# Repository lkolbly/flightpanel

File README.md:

DIY Flightpanel
===============

Welcome to my DIY flightpanel. There are three components to this project:

* Mechanical design
* PCB design
* Firmware

All three are custom-built for this project.

PCB
===

The PCB has support for up to the following inputs:

* 16x push buttons
* 14x double-throw switches
* 6x rotary encoders with push-buttons
* 10x potentiometers or hall-effect sensors

(note that Windows only supports up to 8 axes)

Mechanical
==========

The mechanical design is in FreeCAD, in the `flightpanel.FCStd` file. Within
that project look at the Assembly for a reference design with all included
components, including stand-ins for various knobs and switches.

The design is oriented around providing a standardized base, with swappable
control scheme panels. Each panel has a working area of 60mm wide by 100mm tall
- see BigPanelTemplate in the FreeCAD project for a template. Two panels may be
combined to create a "wide" 128mm by 100mm panel.

The panel should extend 3.5mm past the centers of the holes for optimum
mechanical support.

The core structure provides space for up to 6 panels - two on the front face,
two on the top face (with an approximately 30 degree slope), and one on each
side.

The core consists of the following parts:
- `StructureFront`
- `StructureTop`
- `StructureBase`
- `SidePanel`

The mounting on the back is two M6 holes spaced 40mm apart vertically. Mouse bites are provided for additional rigidity. The `Mount` part provides a reference design for a mount - as modelled, for mounting to a 35mm wide square tube.

Hardware required for assembly:
- Heat-set M3 threaded inserts, designed for a 4.5mm diameter hole with 5mm depth.
- 14 to 38x M3 by 8mm bolts (14 for structure assembly, up to 24 for mounting panels).
- 2x M6 by 20mm bolts with nuts.

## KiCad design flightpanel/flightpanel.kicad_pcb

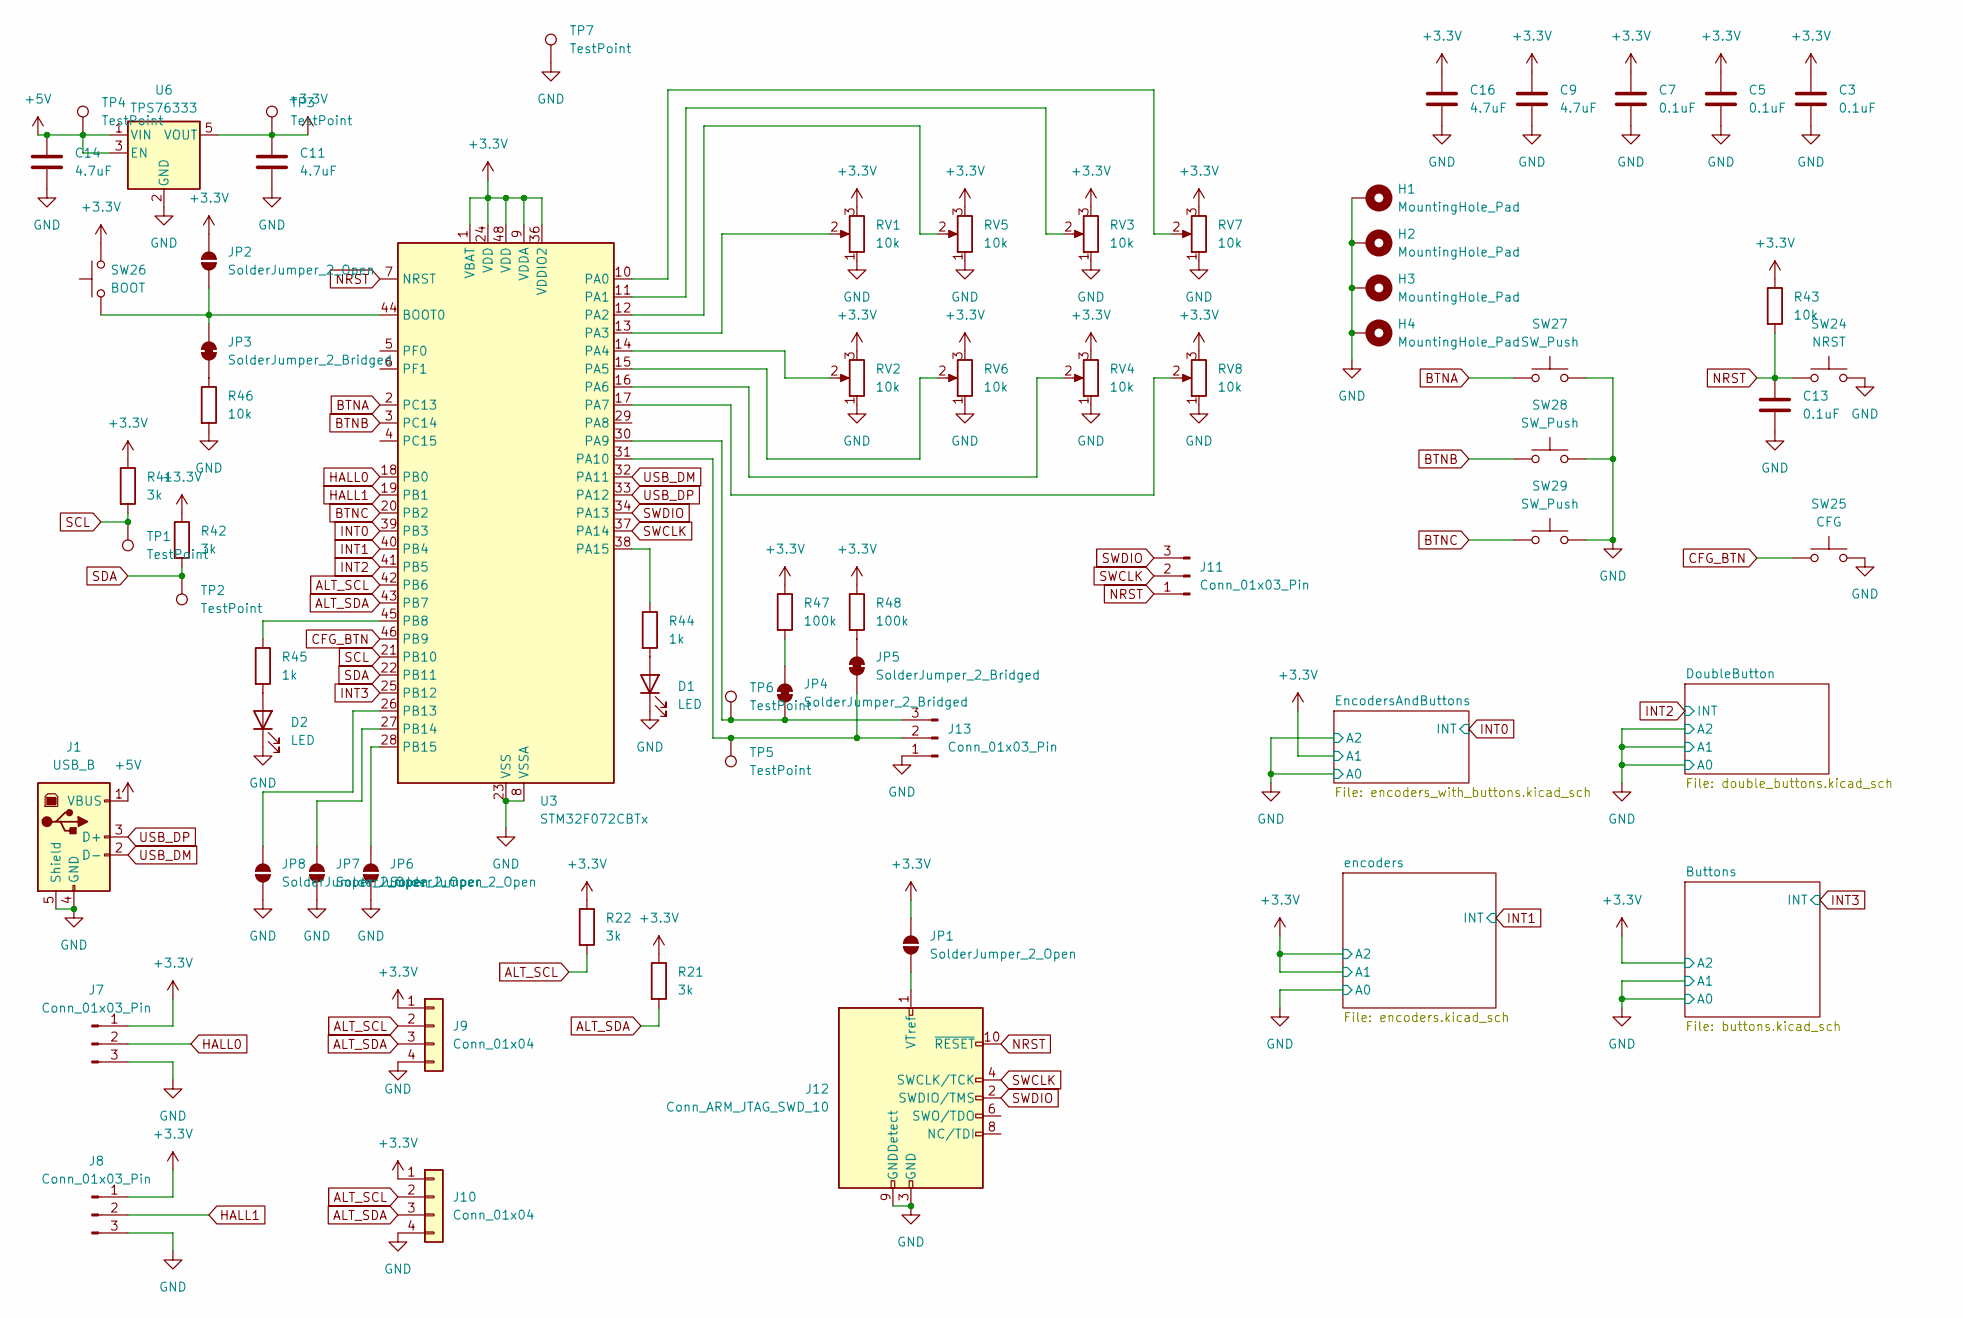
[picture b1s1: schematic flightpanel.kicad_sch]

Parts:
C3, C5, C7, C13: 0.1uF; C_0603_1608Metric; LCSC Part Number C14663
C9, C11, C14, C16: 4.7uF; C_0603_1608Metric; LCSC Part Number C19666
D1, D2: LED; LED_0603_1608Metric; LCSC Part Number C2286
H1, H2, H3, H4: MountingHole_Pad; MountingHole_3.2mm_M3_Pad
J1: USB_B; USB-B-TH_USB-B10-BRW; LCSC Part Number C720549
J7, J8, J11: Conn_01x03_Pin; PinHeader_1x03_P2.54mm_Vertical
J9, J10: Conn_01x04; PinHeader_1x04_P2.54mm_Vertical
J12: Conn_ARM_JTAG_SWD_10; PinHeader_2x05_P1.27mm_Vertical; LCSC Part Number C239059
J13: Conn_01x03_Pin; PinHeader_1x03_P2.54mm_Vertical; LCSC Part Number C146690
JP1, JP2, JP6, JP7, JP8: SolderJumper_2_Open; SolderJumper-2_P1.3mm_Open_RoundedPad1.0x1.5mm
JP3, JP4, JP5: SolderJumper_2_Bridged; SolderJumper-2_P1.3mm_Bridged_RoundedPad1.0x1.5mm
R21, R22, R41, R42: 3k; R_0603_1608Metric; LCSC Part Number C4211
R43, R46: 10k; R_0603_1608Metric; LCSC Part Number C25804
R44, R45: 1k; R_0603_1608Metric; LCSC Part Number C21190
R47, R48: 100k; R_0603_1608Metric; LCSC Part Number C25803
RV1, RV2, RV3, RV4, RV5, RV6, RV7, RV8: 10k; PinSocket_1x03_P2.54mm_Vertical; LCSC Part Number C146690
SW24: NRST; SW-SMD_L3.9-W3.0-P4.45; LCSC Part Number C720477
SW25: CFG; SW-SMD_L3.9-W3.0-P4.45; LCSC Part Number C720477
SW26: BOOT; SW-SMD_L3.9-W3.0-P4.45; LCSC Part Number C720477
SW27, SW28, SW29: SW_Push; PinSocket_1x02_P2.54mm_Vertical; LCSC Part Number C49661
TP1, TP2, TP3, TP4, TP5, TP6, TP7: TestPoint; TestPoint_Pad_D2.0mm
U3: STM32F072CBTx; LQFP-48_7x7mm_P0.5mm; LCSC Part Number C81720
U6: TPS76333; SOT-23-5; LCSC Part Number C7100

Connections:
+3.3V: C3.1, C5.1, C7.1, C9.1, C11.1, C16.1, J7.1, J8.1, J9.1, J10.1, JP1.2 (B), JP2.2 (B), R21.1, R22.1, R41.1, R42.1, R43.1, R47.1, R48.1, RV1.3, RV2.3, RV3.3, RV4.3, RV5.3, RV6.3, RV7.3, RV8.3, SW26.2, TP3.1, U3.1 (VBAT), U3.9 (VDDA), U3.24 (VDD), U3.36 (VDDIO2), U3.48 (VDD), U6.5 (VOUT); also elsewhere on the board
+5V: C14.1, J1.1 (VBUS), TP4.1, U6.1 (VIN), U6.3 (EN)
ALT_SCL: J9.2, J10.2, R22.2, U3.42 (PB6)
ALT_SDA: J9.3, J10.3, R21.2, U3.43 (PB7)
BTNA: SW27.1, U3.2 (PC13)
BTNB: SW28.1, U3.3 (PC14)
BTNC: SW29.1, U3.20 (PB2)
CFG_BTN: SW25.1, U3.46 (PB9)
GND: C3.2, C5.2, C7.2, C9.2, C11.2, C13.2, C14.2, C16.2, D1.1 (K), D2.1 (K), H1.1, H2.1, H3.1, H4.1, J1.4 (GND), J1.5 (Shield), J7.3, J8.3, J9.4, J10.4, J12.3 (GND), J12.5 (GND), J12.9 (GNDDetect), J13.1, JP6.1 (A), JP7.1 (A), JP8.1 (A), R46.2, RV1.1, RV2.1, RV3.1, RV4.1, RV5.1, RV6.1, RV7.1, RV8.1, SW24.2, SW25.2, SW27.2, SW28.2, SW29.2, TP7.1, U3.8 (VSSA), U3.23 (VSS), U3.35 (VSS), U3.47 (VSS), U6.2 (GND); also elsewhere on the board
HALL0: J7.2, U3.18 (PB0)
HALL1: J8.2, U3.19 (PB1)
INT0: U3.39 (PB3); also elsewhere on the board
INT1: U3.40 (PB4); also elsewhere on the board
INT2: U3.41 (PB5); also elsewhere on the board
INT3: U3.25 (PB12); also elsewhere on the board
NRST: C13.1, J11.1, J12.10 (~RESET), R43.2, SW24.1, U3.7 (NRST)
unnamed: D1.2 (A), R44.2
unnamed: D2.2 (A), R45.2
unnamed: J12.1 (VTref), JP1.1 (A)
unnamed: J13.2, JP5.1 (A), TP5.1, U3.31 (PA10)
unnamed: J13.3, JP4.1 (A), TP6.1, U3.30 (PA9)
unnamed: JP2.1 (A), JP3.2 (B), SW26.1, U3.44 (BOOT0)
unnamed: JP3.1 (A), R46.1
unnamed: JP4.2 (B), R47.2
unnamed: JP5.2 (B), R48.2
unnamed: JP6.2 (B), U3.28 (PB15)
unnamed: JP7.2 (B), U3.27 (PB14)
unnamed: JP8.2 (B), U3.26 (PB13)
unnamed: RV7.2, U3.10 (PA0)
unnamed: RV3.2, U3.11 (PA1)
unnamed: RV5.2, U3.12 (PA2)
unnamed: RV1.2, U3.13 (PA3)
unnamed: RV2.2, U3.14 (PA4)
unnamed: RV6.2, U3.15 (PA5)
unnamed: RV4.2, U3.16 (PA6)
unnamed: RV8.2, U3.17 (PA7)
unnamed: R44.1, U3.38 (PA15)
unnamed: R45.1, U3.45 (PB8)
SCL: R41.2, TP1.1, U3.21 (PB10); also elsewhere on the board
SDA: R42.2, TP2.1, U3.22 (PB11); also elsewhere on the board
SWCLK: J11.2, J12.4 (SWCLK/TCK), U3.37 (PA14)
SWDIO: J11.3, J12.2 (SWDIO/TMS), U3.34 (PA13)
USB_DM: J1.2 (D-), U3.32 (PA11)
USB_DP: J1.3 (D+), U3.33 (PA12)

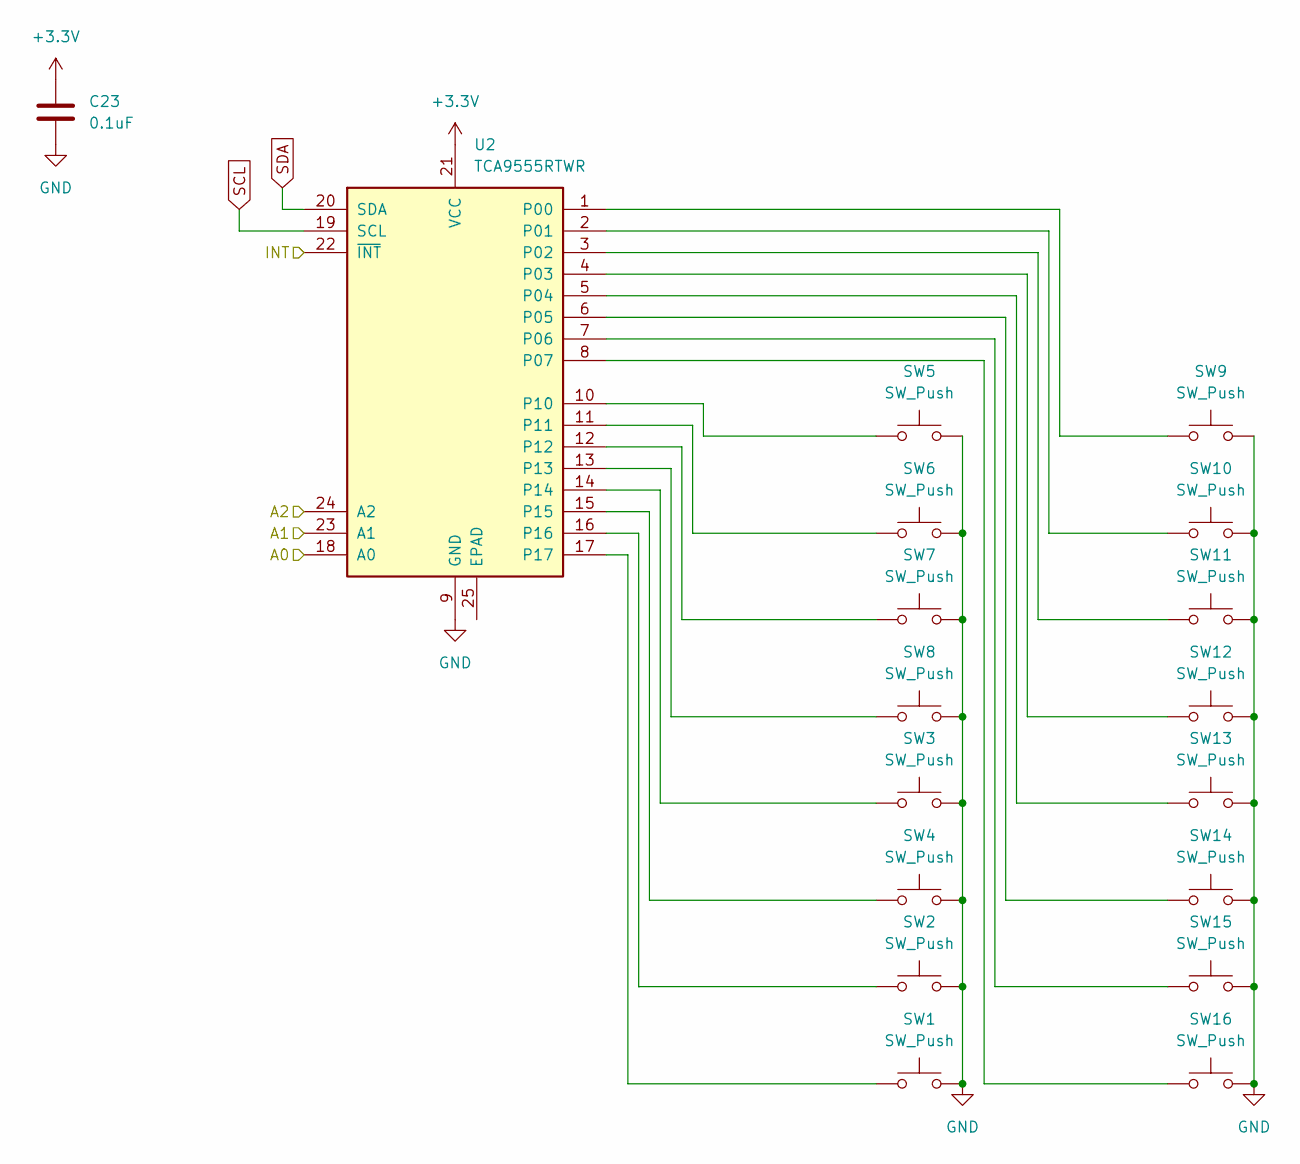
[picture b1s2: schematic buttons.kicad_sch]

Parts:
C23: 0.1uF; C_0603_1608Metric; LCSC Part Number C14663
SW1, SW2, SW3, SW4, SW5, SW6, SW7, SW8, SW9, SW10, SW11, SW12, SW13, SW14, SW15, SW16: SW_Push; PinSocket_1x02_P2.54mm_Vertical; LCSC Part Number C49661
U2: TCA9555RTWR; WQFN-24-1EP_4x4mm_P0.5mm_EP2.45x2.45mm; LCSC Part Number C140277

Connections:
+3.3V: C23.1, U2.21 (VCC), U2.24 (A2); also elsewhere on the board
GND: C23.2, SW1.2, SW2.2, SW3.2, SW4.2, SW5.2, SW6.2, SW7.2, SW8.2, SW9.2, SW10.2, SW11.2, SW12.2, SW13.2, SW14.2, SW15.2, SW16.2, U2.9 (GND), U2.18 (A0), U2.23 (A1); also elsewhere on the board
INT3: U2.22 (~INT); also elsewhere on the board
unnamed: SW9.1, U2.1 (P00)
unnamed: SW10.1, U2.2 (P01)
unnamed: SW11.1, U2.3 (P02)
unnamed: SW12.1, U2.4 (P03)
unnamed: SW13.1, U2.5 (P04)
unnamed: SW14.1, U2.6 (P05)
unnamed: SW15.1, U2.7 (P06)
unnamed: SW16.1, U2.8 (P07)
unnamed: SW5.1, U2.10
unnamed: SW6.1, U2.11
unnamed: SW7.1, U2.12
unnamed: SW8.1, U2.13
unnamed: SW3.1, U2.14
unnamed: SW4.1, U2.15
unnamed: SW2.1, U2.16
unnamed: SW1.1, U2.17
SCL: U2.19 (SCL); also elsewhere on the board
SDA: U2.20 (SDA); also elsewhere on the board

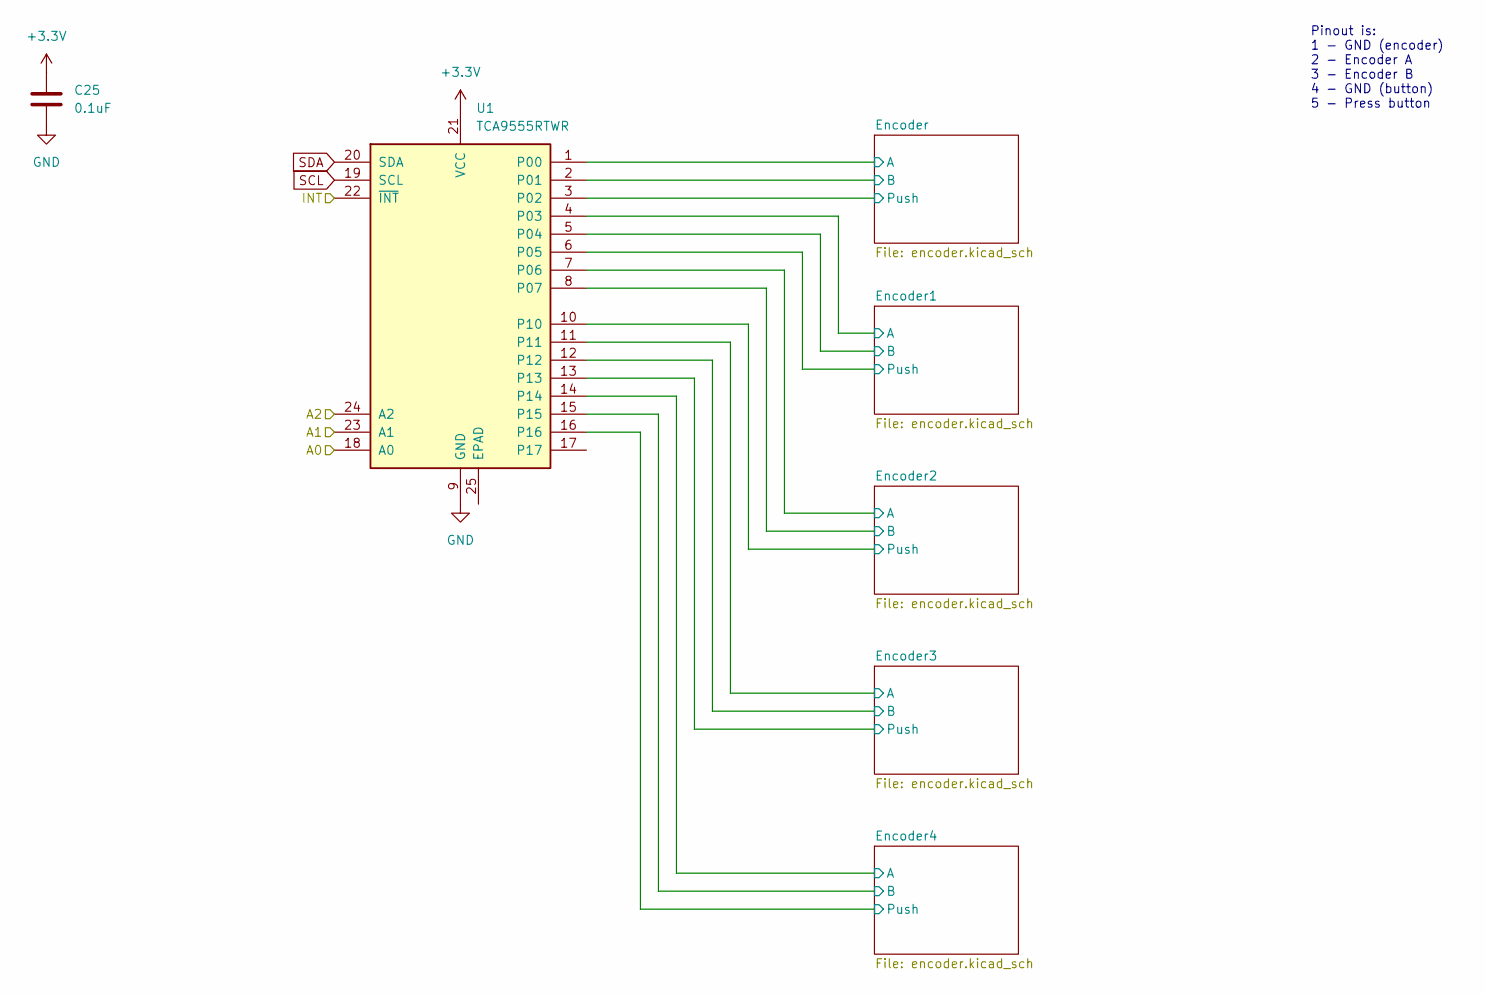
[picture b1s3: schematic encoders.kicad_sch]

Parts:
C25: 0.1uF; C_0603_1608Metric; LCSC Part Number C14663
U1: TCA9555RTWR; WQFN-24-1EP_4x4mm_P0.5mm_EP2.45x2.45mm; LCSC Part Number C140277

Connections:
+3.3V: C25.1, U1.21 (VCC), U1.23 (A1), U1.24 (A2); also elsewhere on the board
/encoders/Encoder1/A: U1.4 (P03); also elsewhere on the board
/encoders/Encoder1/B: U1.5 (P04); also elsewhere on the board
/encoders/Encoder1/Push: U1.6 (P05); also elsewhere on the board
/encoders/Encoder2/A: U1.7 (P06); also elsewhere on the board
/encoders/Encoder2/B: U1.8 (P07); also elsewhere on the board
/encoders/Encoder2/Push: U1.10; also elsewhere on the board
/encoders/Encoder3/A: U1.11; also elsewhere on the board
/encoders/Encoder3/B: U1.12; also elsewhere on the board
/encoders/Encoder3/Push: U1.13; also elsewhere on the board
/encoders/Encoder4/A: U1.14; also elsewhere on the board
/encoders/Encoder4/B: U1.15; also elsewhere on the board
/encoders/Encoder4/Push: U1.16; also elsewhere on the board
/encoders/Encoder/A: U1.1 (P00); also elsewhere on the board
/encoders/Encoder/B: U1.2 (P01); also elsewhere on the board
/encoders/Encoder/Push: U1.3 (P02); also elsewhere on the board
GND: C25.2, U1.9 (GND), U1.18 (A0); also elsewhere on the board
INT1: U1.22 (~INT); also elsewhere on the board
SCL: U1.19 (SCL); also elsewhere on the board
SDA: U1.20 (SDA); also elsewhere on the board

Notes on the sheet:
Pinout is: 1 - GND (encoder) 2 - Encoder A 3 - Encoder B 4 - GND (button) 5 - Press button

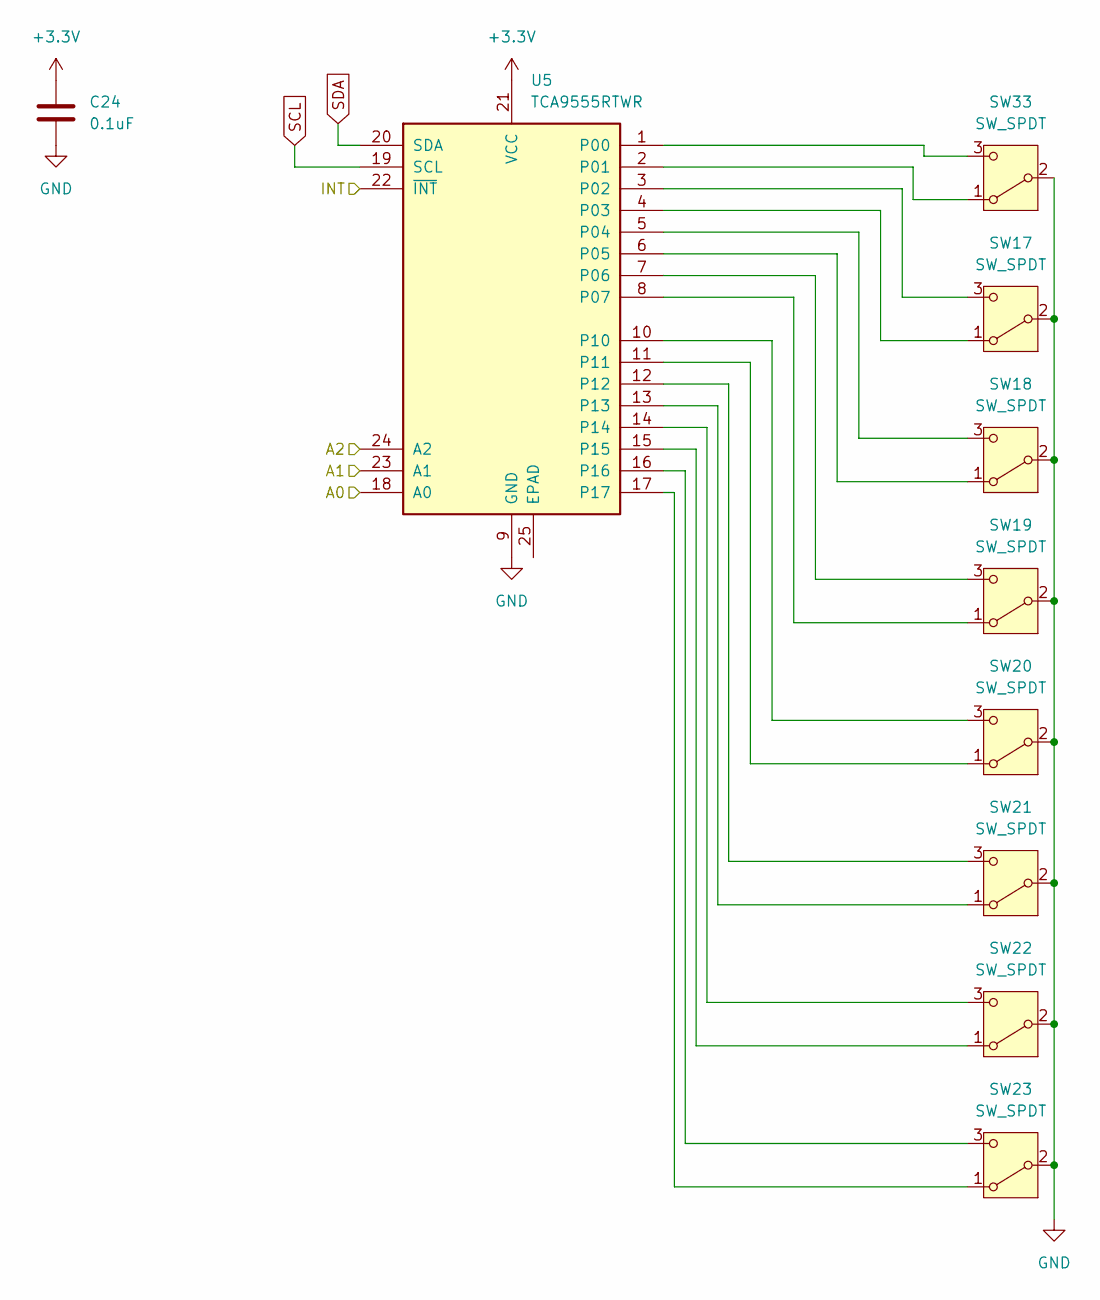
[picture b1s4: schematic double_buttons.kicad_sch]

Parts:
C24: 0.1uF; C_0603_1608Metric; LCSC Part Number C14663
SW17, SW18, SW19, SW20, SW21, SW22, SW23, SW33: SW_SPDT; PinSocket_1x03_P2.54mm_Vertical; LCSC Part Number C146690
U5: TCA9555RTWR; WQFN-24-1EP_4x4mm_P0.5mm_EP2.45x2.45mm; LCSC Part Number C140277

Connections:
+3.3V: C24.1, U5.21 (VCC); also elsewhere on the board
GND: C24.2, SW17.2 (B), SW18.2 (B), SW19.2 (B), SW20.2 (B), SW21.2 (B), SW22.2 (B), SW23.2 (B), SW33.2 (B), U5.9 (GND), U5.18 (A0), U5.23 (A1), U5.24 (A2); also elsewhere on the board
INT2: U5.22 (~INT); also elsewhere on the board
unnamed: SW17.1 (A), U5.4 (P03)
unnamed: SW17.3 (C), U5.3 (P02)
unnamed: SW18.1 (A), U5.6 (P05)
unnamed: SW18.3 (C), U5.5 (P04)
unnamed: SW19.1 (A), U5.8 (P07)
unnamed: SW19.3 (C), U5.7 (P06)
unnamed: SW20.1 (A), U5.11
unnamed: SW20.3 (C), U5.10
unnamed: SW21.1 (A), U5.13
unnamed: SW21.3 (C), U5.12
unnamed: SW22.1 (A), U5.15
unnamed: SW22.3 (C), U5.14
unnamed: SW23.1 (A), U5.17
unnamed: SW23.3 (C), U5.16
unnamed: SW33.1 (A), U5.2 (P01)
unnamed: SW33.3 (C), U5.1 (P00)
SCL: U5.19 (SCL); also elsewhere on the board
SDA: U5.20 (SDA); also elsewhere on the board

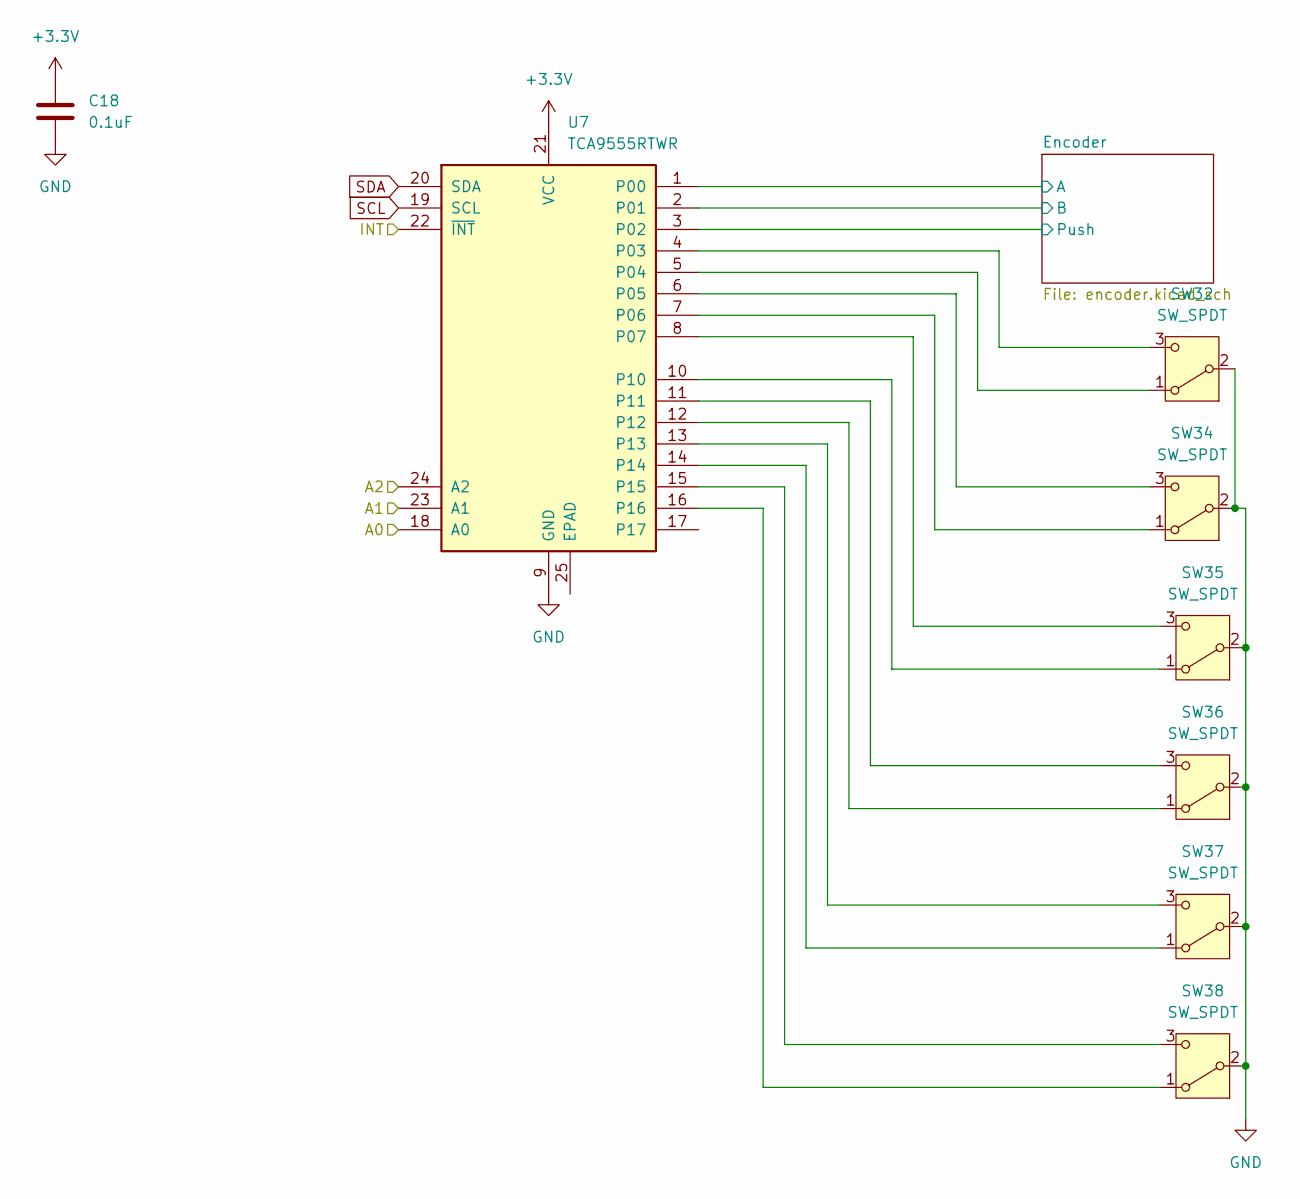
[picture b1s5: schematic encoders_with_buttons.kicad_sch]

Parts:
C18: 0.1uF; C_0603_1608Metric; LCSC Part Number C14663
SW32, SW34, SW35, SW36, SW37, SW38: SW_SPDT; PinSocket_1x03_P2.54mm_Vertical; LCSC Part Number C146690
U7: TCA9555RTWR; WQFN-24-1EP_4x4mm_P0.5mm_EP2.45x2.45mm; LCSC Part Number C140277

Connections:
+3.3V: C18.1, U7.21 (VCC), U7.23 (A1); also elsewhere on the board
/EncodersAndButtons/Encoder/A: U7.1 (P00); also elsewhere on the board
/EncodersAndButtons/Encoder/B: U7.2 (P01); also elsewhere on the board
/EncodersAndButtons/Encoder/Push: U7.3 (P02); also elsewhere on the board
GND: C18.2, SW32.2 (B), SW34.2 (B), SW35.2 (B), SW36.2 (B), SW37.2 (B), SW38.2 (B), U7.9 (GND), U7.18 (A0), U7.24 (A2); also elsewhere on the board
INT0: U7.22 (~INT); also elsewhere on the board
unnamed: SW32.1 (A), U7.5 (P04)
unnamed: SW32.3 (C), U7.4 (P03)
unnamed: SW34.1 (A), U7.7 (P06)
unnamed: SW34.3 (C), U7.6 (P05)
unnamed: SW35.1 (A), U7.10
unnamed: SW35.3 (C), U7.8 (P07)
unnamed: SW36.1 (A), U7.12
unnamed: SW36.3 (C), U7.11
unnamed: SW37.1 (A), U7.14
unnamed: SW37.3 (C), U7.13
unnamed: SW38.1 (A), U7.16
unnamed: SW38.3 (C), U7.15
SCL: U7.19 (SCL); also elsewhere on the board
SDA: U7.20 (SDA); also elsewhere on the board

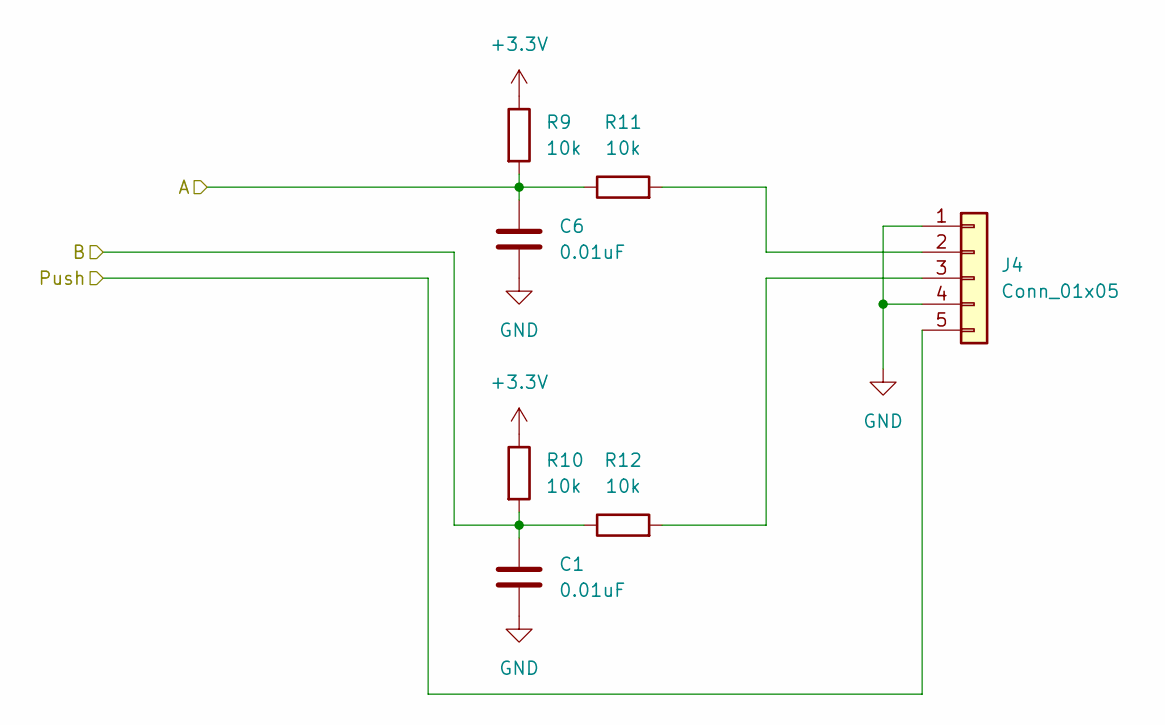
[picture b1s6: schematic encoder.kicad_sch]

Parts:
C1, C6: 0.01uF; C_0603_1608Metric; LCSC Part Number C57112
J4: Conn_01x05; PinSocket_1x05_P2.54mm_Vertical; LCSC Part Number C50950
R9, R10, R11, R12: 10k; R_0603_1608Metric; LCSC Part Number C25804

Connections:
+3.3V: R9.1, R10.1; also elsewhere on the board
/encoders/Encoder/A: C6.1, R9.2, R11.1; also elsewhere on the board
/encoders/Encoder/B: C1.1, R10.2, R12.1; also elsewhere on the board
/encoders/Encoder/Push: J4.5; also elsewhere on the board
GND: C1.2, C6.2, J4.1, J4.4; also elsewhere on the board
unnamed: J4.2, R11.2
unnamed: J4.3, R12.2

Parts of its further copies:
C2, C4, C8, C10, C12, C20, C22, C27, C28, C29: 0.01uF; C_0603_1608Metric; LCSC Part Number C57112
J2, J3, J5, J6, J14: Conn_01x05; PinSocket_1x05_P2.54mm_Vertical; LCSC Part Number C50950
R1, R2, R3, R4, R5, R6, R7, R8, R13, R14, R15, R16, R17, R18, R19, R20, R49, R50, R51, R52: 10k; R_0603_1608Metric; LCSC Part Number C25804

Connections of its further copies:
+3.3V: R1.1, R2.1, R5.1, R6.1, R13.1, R14.1, R17.1, R18.1, R49.1, R50.1; also elsewhere on the board
/EncodersAndButtons/Encoder/A: C20.1, R49.2, R51.1; also elsewhere on the board
/EncodersAndButtons/Encoder/B: C22.1, R50.2, R52.1; also elsewhere on the board
/EncodersAndButtons/Encoder/Push: J14.5; also elsewhere on the board
/encoders/Encoder1/A: C2.1, R1.2, R3.1; also elsewhere on the board
/encoders/Encoder1/B: C12.1, R2.2, R4.1; also elsewhere on the board
/encoders/Encoder1/Push: J2.5; also elsewhere on the board
/encoders/Encoder2/A: C4.1, R5.2, R7.1; also elsewhere on the board
/encoders/Encoder2/B: C27.1, R6.2, R8.1; also elsewhere on the board
/encoders/Encoder2/Push: J3.5; also elsewhere on the board
/encoders/Encoder3/A: C8.1, R13.2, R15.1; also elsewhere on the board
/encoders/Encoder3/B: C28.1, R14.2, R16.1; also elsewhere on the board
/encoders/Encoder3/Push: J5.5; also elsewhere on the board
/encoders/Encoder4/A: C10.1, R17.2, R19.1; also elsewhere on the board
/encoders/Encoder4/B: C29.1, R18.2, R20.1; also elsewhere on the board
/encoders/Encoder4/Push: J6.5; also elsewhere on the board
GND: C2.2, C4.2, C8.2, C10.2, C12.2, C20.2, C22.2, C27.2, C28.2, C29.2, J2.1, J2.4, J3.1, J3.4, J5.1, J5.4, J6.1, J6.4, J14.1, J14.4; also elsewhere on the board
unnamed: J2.2, R3.2
unnamed: J2.3, R4.2
unnamed: J3.2, R7.2
unnamed: J3.3, R8.2
unnamed: J5.2, R15.2
unnamed: J5.3, R16.2
unnamed: J6.2, R19.2
unnamed: J6.3, R20.2
unnamed: J14.2, R51.2
unnamed: J14.3, R52.2

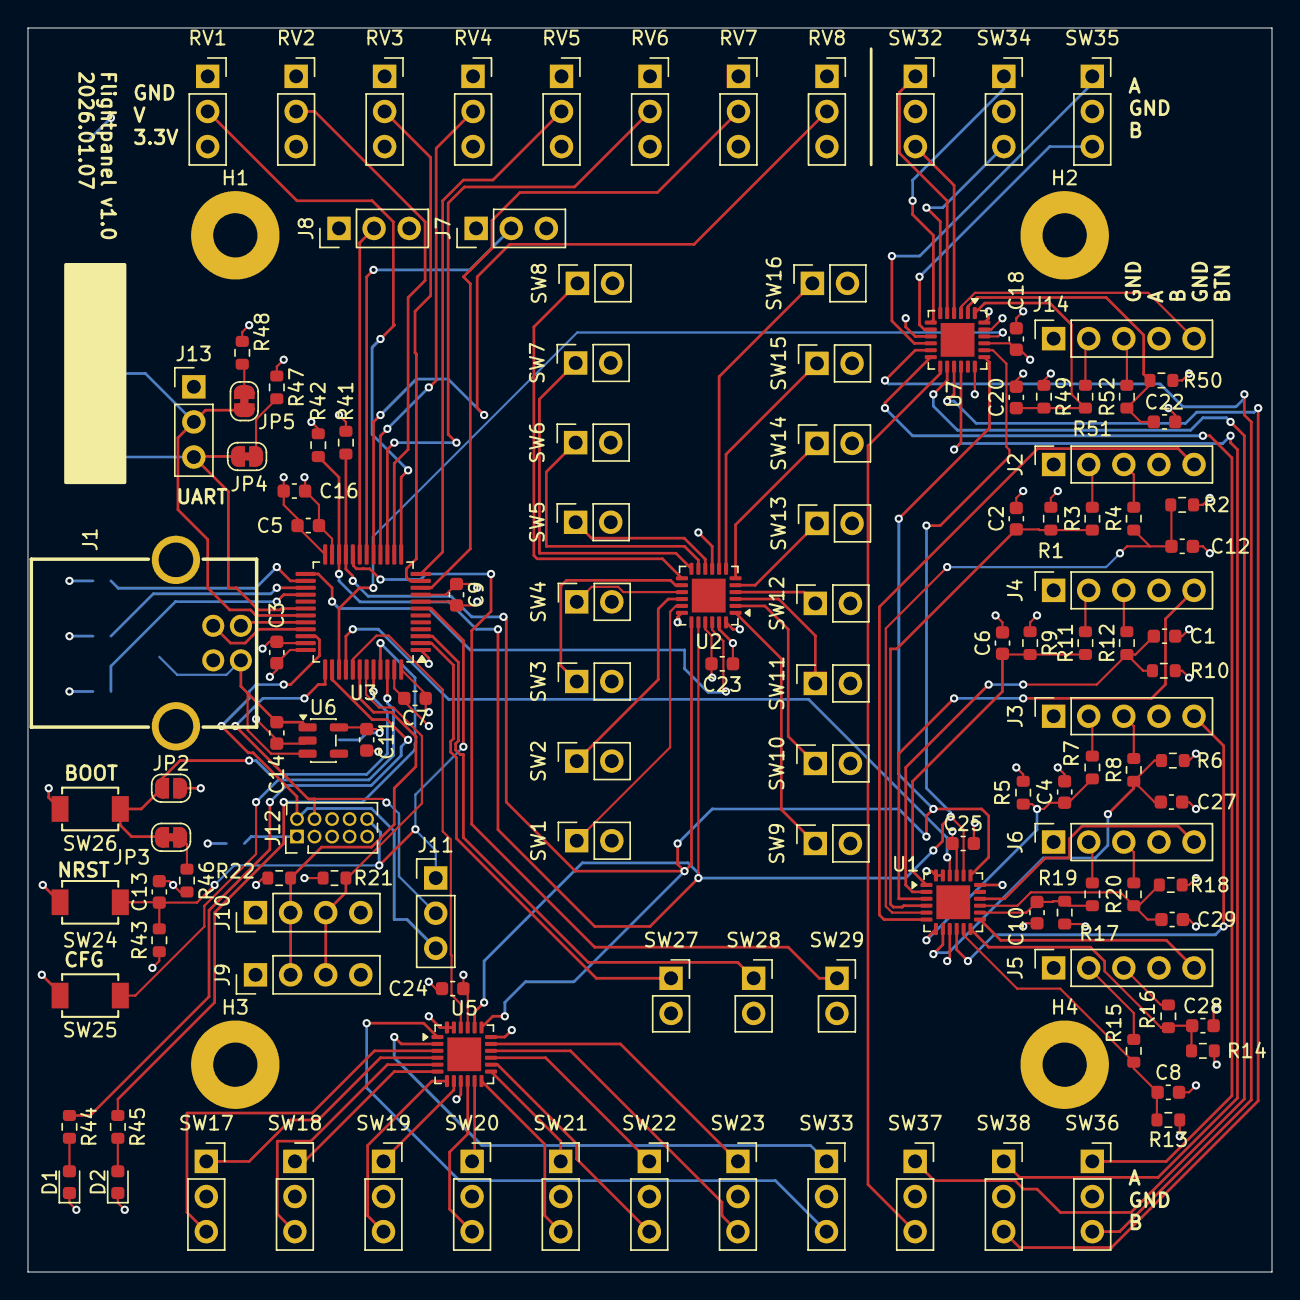
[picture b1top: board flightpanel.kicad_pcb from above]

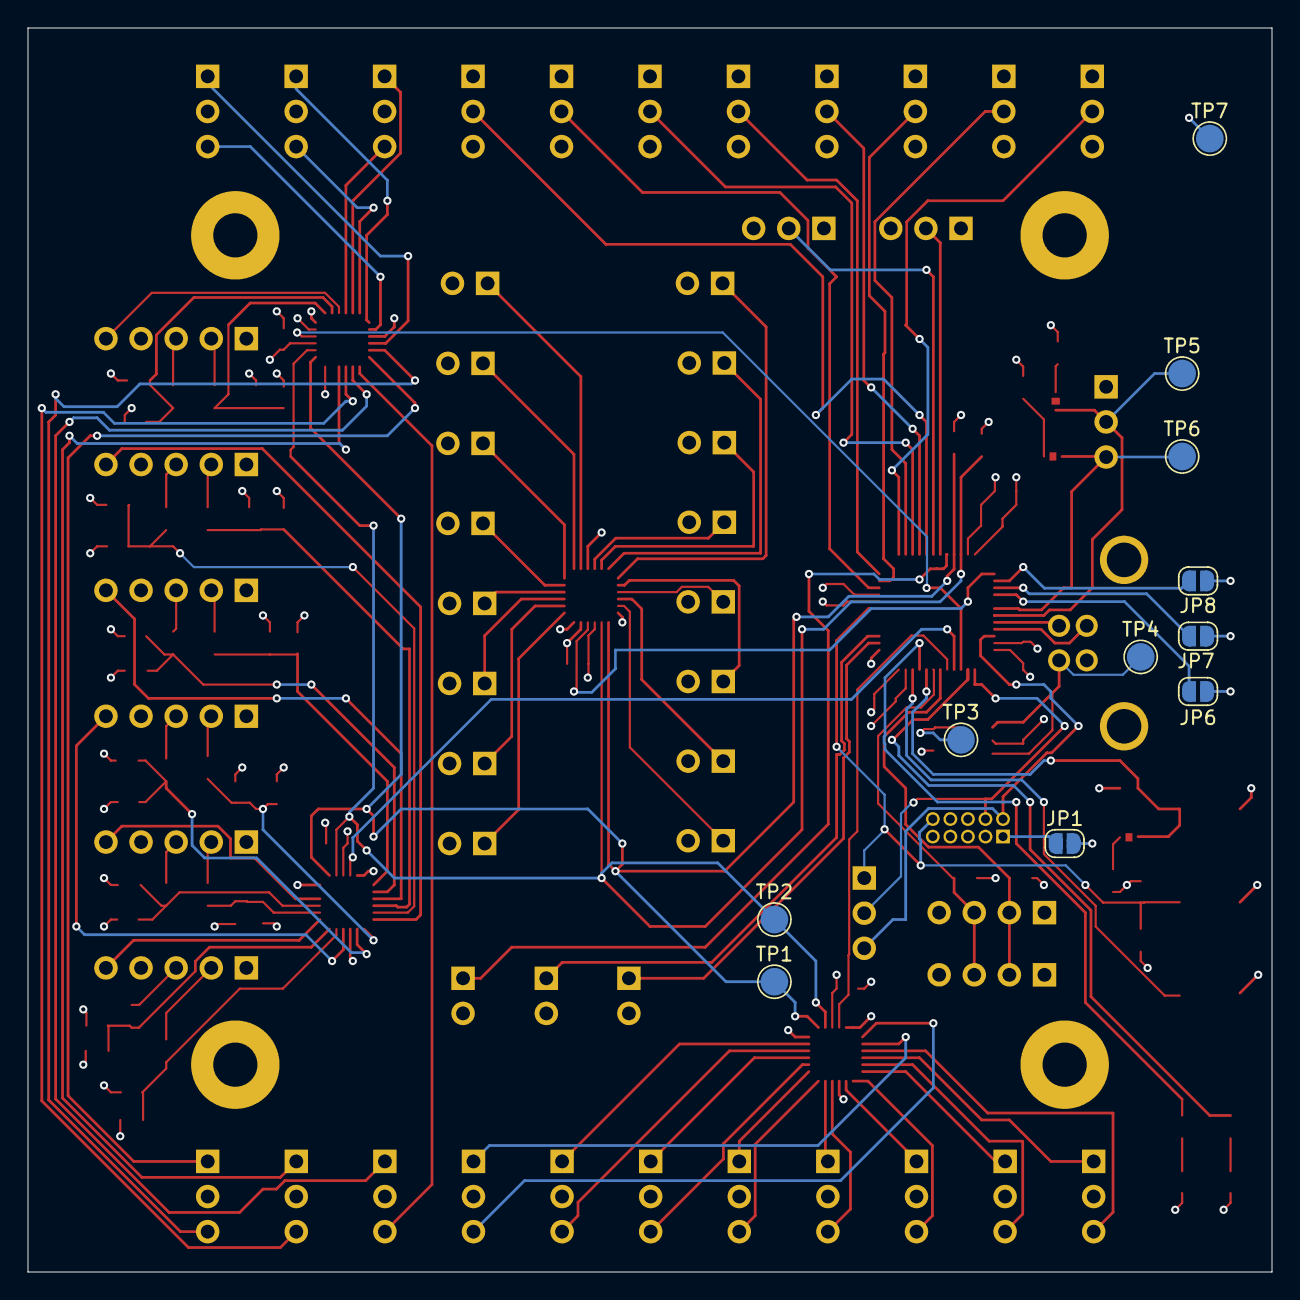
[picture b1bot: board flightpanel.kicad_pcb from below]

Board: 4 copper layers, 90.0 x 90.0 mm, 143 parts (11 on the bottom side), 118 nets.

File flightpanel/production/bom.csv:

Designator,Footprint,Quantity,Value,LCSC Part #
"C1, C10, C12, C2, C20, C22, C27, C28, C29, C4, C6, C8",0603,12,0.01uF,C57112
"C11, C14, C16, C9",0603,4,4.7uF,C19666
"C13, C18, C23, C24, C25, C3, C5, C7",0603,8,0.1uF,C14663
"D1, D2",0603,2,LED,C2286
J1,USB-B-TH_USB-B10-BRW,1,USB_B,C720549
"J10, J9",PinHeader_1x04_P2.54mm_Vertical,2,Conn_01x04,
"J11, J7, J8",PinHeader_1x03_P2.54mm_Vertical,3,Conn_01x03_Pin,
J12,PinHeader_2x05_P1.27mm_Vertical,1,Conn_ARM_JTAG_SWD_10,C239059
J13,PinHeader_1x03_P2.54mm_Vertical,1,Conn_01x03_Pin,C146690
"J14, J2, J3, J4, J5, J6",PinSocket_1x05_P2.54mm_Vertical,6,Conn_01x05,C50950
"R1, R10, R11, R12, R13, R14, R15, R16, R17, R18, R19, R2, R20, R3, R4, R43, R46, R49, R5, R50, R51, R52, R6, R7, R8, R9",0603,26,10k,C25804
"R21, R22, R41, R42",0603,4,3k,C4211
"R44, R45",0603,2,1k,C21190
"R47, R48",0603,2,100k,C25803
"RV1, RV2, RV3, RV4, RV5, RV6, RV7, RV8",PinSocket_1x03_P2.54mm_Vertical,8,10k,C146690
"SW1, SW10, SW11, SW12, SW13, SW14, SW15, SW16, SW2, SW27, SW28, SW29, SW3, SW4, SW5, SW6, SW7, SW8, SW9",PinSocket_1x02_P2.54mm_Vertical,19,SW_Push,C49661
"SW17, SW18, SW19, SW20, SW21, SW22, SW23, SW32, SW33, SW34, SW35, SW36, SW37, SW38",PinSocket_1x03_P2.54mm_Vertical,14,SW_SPDT,C146690
SW24,SW-SMD_L3.9-W3.0-P4.45,1,NRST,C720477
SW25,SW-SMD_L3.9-W3.0-P4.45,1,CFG,C720477
SW26,SW-SMD_L3.9-W3.0-P4.45,1,BOOT,C720477
"TP1, TP2, TP3, TP4, TP5, TP6, TP7",TestPoint_Pad_D2.0mm,7,TestPoint,
"U1, U2, U5, U7",WQFN-24-1EP_4x4mm_P0.5mm_EP2.45x2.45mm,4,TCA9555RTWR,C140277
U3,LQFP-48_7x7mm_P0.5mm,1,STM32F072CBTx,C81720
U6,SOT-23-5,1,TPS76333,C7100

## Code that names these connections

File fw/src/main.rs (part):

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    gpio::{Input as GpioInput, Level, Output, Speed},
    i2c::{self, I2c, Master},
    mode::Async,
    peripherals::{self, ADC1, DMA1_CH4, PA8, PB8, USB},
    rcc::mux::ClockMux,
    time::Hertz,
    usb::{self, Driver, Instance},
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#[panic_handler]
fn panic(info: &PanicInfo) -> ! {
    // Safety: We've panicked
    let pb8 = unsafe { PB8::steal() };
    let mut led = Output::new(pb8, Level::Low, Speed::Low);

    loop {
        let count = PANIC_COUNT.load(core::sync::atomic::Ordering::SeqCst);
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    }

    let p = embassy_stm32::init(config);
    let mut led = Output::new(p.PB8, Level::Low, Speed::Low);

    let mut int0 = GpioInput::new(p.PB3, embassy_stm32::gpio::Pull::Up);
    let mut int1 = GpioInput::new(p.PB4, embassy_stm32::gpio::Pull::Up);
    let mut int2 = GpioInput::new(p.PB5, embassy_stm32::gpio::Pull::Up);
    let mut int3 = GpioInput::new(p.PB12, embassy_stm32::gpio::Pull::Up);

    let mut adc = Adc::new(p.ADC1, Irqs);
    let vref = adc.enable_vref();
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    i2c_config.frequency = Hertz::khz(400);
    i2c_config.timeout = Duration::from_millis(50);
    let mut i2c = I2c::new(
        p.I2C2, p.PB10, p.PB11, p.DMA1_CH4, p.DMA1_CH5, Irqs, i2c_config,
    );

    let driver = Driver::new(p.USB, Irqs, p.PA12, p.PA11);

    // Note: This VID/PID is a reserved testing PID
    let mut config = embassy_usb::Config::new(0x1209, 0x000d);
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    let task = adc_task(
        adc,
        [
            p.PA0.degrade_adc(),
            p.PA1.degrade_adc(),
            p.PA2.degrade_adc(),
            p.PA3.degrade_adc(),
            p.PA4.degrade_adc(),
            p.PA5.degrade_adc(),
            p.PA6.degrade_adc(),
            p.PA7.degrade_adc(),
        ],
        vref.degrade_adc(),
    )
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
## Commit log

2026-01-10 Initial commit, v1.0
2026-01-10 Add readme
2026-01-11 Various tweaks
2026-01-24 Serial USB
2026-03-10 Working firmware, update HW to fix collisions
2026-03-11 Minor changes
